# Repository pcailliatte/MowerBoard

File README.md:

# MowerBoard

---

**MowerBoard** est une unité de contrôle électronique (ECU) alternative, robuste et 100% open-source pour tracteurs tondeuses autoportées thermiques.

L'objectif principal de ce projet est de fournir une solution logicielle et matérielle entièrement libre. En mettant à disposition l'intégralité des schémas de conception, des fichiers de fabrication et du code source, nous démocratisons l'accès à une technologie généralement propriétaire et verrouillée par les fabricants.

---

---

## ⚡ À Propos de ce Projet

> **⚠️ Important :** Je suis un **maker amateur passionné par l'électronique**, pas un professionnel de l'ingénierie ni de la motoculture. 
> 
> Ce projet est développé **sur mon temps libre** et représente mon apprentissage et mes expériences personnelles. **Il peut contenir des erreurs de conception, des mauvaises pratiques ou des défauts** que je ne pourrais pas identifier seul.
>
> Je partage ce travail dans un esprit collaboratif et éducatif. Si tu utilises ce projet, sois conscient que :
> - La conception peut ne pas être optimale
> - Il n'y a pas de validation professionnelle ou de certification
> - Des améliorations et corrections peuvent être nécessaires
> - **Toute erreur reste ta responsabilité personnelle**
> - Le support n'est disponible que sur la base du temps libre disponible
>
> **Je t'encourage vivement à faire review ta réalisation par un professionnel** avant une utilisation critique.

---

## 📋 Table des matières

- [À Propos de ce Projet](#-à-propos-de-ce-projet)
- [Machine Cible](#-machine-cible)
- [État du projet](#-état-du-projet)
- [Caractéristiques principales](#-caractéristiques-principales)
- [Spécifications techniques](#-spécifications-techniques)
- [Télémétrie & Home Assistant](#-télémétrie--home-assistant)
- [Coût estimé](#-coût-estimé)
- [Installation & Démarrage](#-installation--démarrage)
- [Structure du projet](#-structure-du-projet)
- [Clause de non-responsabilité](#-clause-de-non-responsabilité--risques-critiques)
- [Licence](#-licence)
- [Contributions](#-contributions--état-du-projet)

---

## 🎯 Machine Cible

**MowerBoard** a été conçu et développé pour : **STAUB BLIZZARD 107 L 16 KH (2019)**

- **Moteur :** EMAK K1600 AVD (16 ch, 452 cm³)
- **Année :** 2019
- **Tension système :** 12V batterie

Cette ECU remplace le contrôleur d'origine de ce tracteur de pelouse, offrant une solution open-source robuste et facilement hackable.

### Portabilité & Forks

Bien que spécifiquement adapté au STAUB BLIZZARD 107 L, le design modulaire permet des adaptations pour d'autres tracteurs de pelouse avec architecture similaire.

Si tu adaptes pour un autre modèle, crée un fork et documente tes changements ! 🍴

---

## 🚦 État du projet

| Aspect | Statut |
|--------|--------|
| **Statut global** | 🛠️ Développement en cours |
| **Phase actuelle** | 🧪 Version alpha |
| **Hardware** | ✅ Saisie terminée (KiCad 10) |
| **Firmware** | 🔄 Écriture initiale en cours (C brut, microcontrôleur AVR) |
| **Structure du dépôt** | 🔄 Organisation en cours |
| **Documentation** | 🔄 En cours |
| **Release stable** | ⏳ Non disponible |

---

## 🚀 Caractéristiques principales

*   **✨ Matériel et Code 100% Libres :** Accès total aux schémas électroniques, fichiers de routage (PCB) et code source du firmware sans restriction d'accès. Inspiré par la philosophie du mouvement open-source.

*   **🛡️ Architecture Robuste :** Conçu spécifiquement pour l'environnement difficile d'un véhicule thermique (vibrations, parasites électromagnétiques induits par l'allumage, variations de tension de batterie, humidité).

*   **🔒 Logique de Sécurité Centralisée :** Gestion stricte et déterministe des boucles de sécurité critiques :
    - Détection de présence siège
    - Engagement/désengagement des lames
    - Position du point mort
    - Frein de parking
    - Arrêt d'urgence matériel
    - **Failsafe matérielle** : DO_EN en pulldown → coupage automatique des sorties en cas de watchdog

*   **⚡ Contrôle de Puissance Intégré :** Commande directe des actionneurs avec protections adaptées :
    - Embrayage électromagnétique de lame
    - Solénoïde de démarreur
    - Gestion thermique et overcurrent

*   **📊 Diagnostic & Télémétrie LoRa :** Support des interfaces de communication pour logging et diagnostic :
    - Communication série UART
    - **Télémétrie longue portée via LoRa** (Wio-E5-LE de Seeed en modem)
    - Monitoring à distance et diagnostics temps-réel (non-critique pour la sécurité)
    - **Intégration Home Assistant** pour domotique locale

*   **💰 Solution Économique :** Coût matériel estimé **~100€** pour fabriquer une carte (bien inférieur aux solutions propriétaires commerciales)

---

## 🛠 Spécifications Techniques

Le projet est divisé en deux domaines totalement ouverts :

### Architecture

*   **Cœur temps-réel :** AVR128DB (boucles de sécurité déterministes, contrôle des actionneurs)
*   **Modem LoRa :** Wio-E5-LE de Seeed (télémétrie optionnelle, non-critique)
*   **Failsafe matérielle :** DO_EN en pulldown garantit l'arrêt en cas de défaillance du MCU

### Hardware (Matériel)

*   **Outil de conception :** KiCad 10
*   **Fichiers fournis :**
    - Schémas de principe détaillés
    - Routage de puissance et signaux
    - Nomenclature complète (BOM)
    - Fichiers Gerber (prêts pour fabrication PCB)
*   **Microcontrôleur principal :** AVR128DB
*   **Module LoRa :** Wio-E5-LE de Seeed (STM32WLE5xx)
*   **Tensions supportées :** 12V batterie, régulation embarquée

### Firmware (Code)

*   **Langage :** C brut (pas de couche d'abstraction matérielle)
*   **Compilateur :** MPLAB X / XC Compiler
*   **Caractéristiques :**
    - Boucles de sécurité déterministes temps-réel
    - Gestion des modes de veille (économie d'énergie)
    - Communication séries (UART)
    - Watchdog matériel et software
    - Failsafe électronique : perte de contrôle → arrêt automatique

### Module LoRa (Télémétrie)

*   **Module :** Seeed Wio-E5-LE (fonctionne en modem indépendant)
*   **Protocole :** LoRaWAN / LoRa
*   **Fonction :** Transmission longue portée des données de diagnostic et de télémétrie
*   **Avantages :** 
    - Portée jusqu'à plusieurs kilomètres
    - Faible consommation énergétique
    - Non-critique pour la sécurité (arrêt indépendant du LoRa)

---

## 📱 Télémétrie & Home Assistant

Le module LoRa transmet les données de la tondeuse vers une gateway LoRaWAN locale, intégrée dans **Home Assistant**.

### Données remontées

**Phase 1 (MVP) :**
- **Horamètre** : Cumul des heures de fonctionnement
- **Tension batterie** : État de charge et diagnostic

**Phase 2 (futur) :**
- Température moteur
- Cycle des lames
- Diagnostics avancés

### Architecture

```
ECU (Wio-E5-LE) 
    ↓ LoRa
Gateway LoRaWAN Seeed
    ↓ Ethernet/WiFi
Home Assistant (local)
    ↓
Dashboard / Alertes / Automations
```

### Utilité

- **Monitoring à distance** : Suivi de l'état depuis le canapé
- **Historique** : Logs des heures de tonte
- **Alertes** : Notification si batterie faible, etc.
- **Automations** : Intégration avec d'autres services domotiques

> **Note :** La télémétrie est **optionnelle et non-critique**. La tondeuse fonctionne normalement même si le LoRa est déconnecté.

---

## 💰 Coût estimé

**Coût de fabrication prévu : ~100€** (pour une carte complète, pièce unique)

Cette estimation inclut :
- PCB (fabrication industrielle)
- Composants électroniques (résistances, condensateurs, ICs)
- Module LoRa Wio-E5-LE
- Connecteurs et éléments passifs
- Régulateur 12V et protections

**Cette solution est significativement moins coûteuse que les ECU propriétaires du marché**, tout en offrant des capacités équivalentes ou supérieures.

> **Note :** Le coût peut varier selon les fournisseurs, les quantités commandées et les taux de change. Cette estimation est basée sur les prix courants des composants (2024). En production de volume, le coût pourrait être réduit.

---

## 🚀 Installation & Démarrage

### Prérequis

**Pour le Hardware :**
- KiCad 10.0+
- Outils de fabrication PCB (si fabrique soi-même)
- Composants électroniques (voir BOM)

**Pour le Firmware :**
- MPLAB X IDE
- Compiler XC8 (Microchip)
- Programmateur AVR (ex : PICKIT5)

**Pour la Télémétrie (optionnel) :**
- Home Assistant (installation locale)
- Gateway LoRaWAN Seeed (WM1302, etc.)

### Étapes de mise en place

#### 1. Cloner le dépôt
```bash
git clone https://github.com/pcailliatte/MowerBoard.git
cd MowerBoard
```

#### 2. Hardware - Fabriquer la carte
- Ouvrir les fichiers KiCad dans `Hardware/`
- Exporter les fichiers Gerber
- Envoyer à un fabricant PCB (ex : JLCPCB, PCBway)
- Souder les composants (voir BOM pour la liste complète)

#### 3. Firmware - Compiler et flasher
```bash
cd Firmware/
mplab build
# Programmer via AVR ISP
```

#### 4. Télémétrie (optionnel)
- Configurer la gateway LoRaWAN dans Home Assistant
- Flasher le firmware LoRa sur le Wio-E5-LE
- Ajouter les sensors dans Home Assistant

---

## 📁 Structure du projet

⚠️ **La structure du dépôt est actuellement en cours d'organisation. Les chemins et répertoires ci-dessous reflètent la vision finale du projet.**

```
MowerBoard/
├── Hardware/
│   ├── STAUB_BLIZZARD_107L/
│   │   ├── Schematics/      # Schémas électroniques KiCad
│   │   ├── PCB/             # Fichiers de routage et Gerber
│   │   ├── BOM.csv          # Nomenclature des composants
│   │   └── Doc/             # Documentation hardware spécifique
│   └── Generic/             # Composants réutilisables pour autres modèles
├── Firmware/
│   ├── src/                 # Code source C
│   ├── include/             # En-têtes
│   ├── Makefile             # Build configuration
│   └── Doc/                 # Documentation firmware
├── LoRa/
│   ├── src/                 # Code LoRa / Wio-E5-LE
│   ├── telemetry/           # Schéma de télémétrie
│   └── Doc/                 # Documentation LoRa & Home Assistant
├── Doc/
│   ├── assets/              # Images et ressources
│   ├── DESIGN.md            # Rationale de conception
│   ├── ASSEMBLY.md          # Guide d'assemblage
│   ├── SAFETY.md            # Guides de sécurité
│   └── COMPATIBILITY.md     # Compatibilité avec autres modèles
├── README.md                # Ce fichier
├── CONTRIBUTING.md          # Guide de contribution
└── LICENCE.md               # Licence du hardware (CERN-OHL-S v2)

```

---

## ⚠️ Clause de Non-Responsabilité & Risques Critiques

### 🚨 DANGER DE MORT ET DE BLESSURES GRAVES

Un tracteur tondeuse est une machine lourde dotée d'un plateau de coupe rotatif à haute vitesse. **Vos actions de conception, de soudure, de câblage, de programmation et d'intégration de cette carte vous engagent personnellement.**

#### Responsabilité absolue de vos actions

*   L'intégration de cette carte, la modification du faisceau électrique d'origine, le flashage du firmware et le **shunt volontaire ou involontaire** des boucles de sécurité construites **relèvent de votre seule responsabilité légale et pénale.**
*   Une défaillance de cette ECU peut entraîner :
    - La perte de contrôle du moteur
    - L'engagement involontaire des lames de coupe
    - La perte du freinage d'urgence
    - **Des blessures graves ou mortelles**

#### Absence de Garantie

Ce projet est fourni **"en l'état"**, à des fins éducatives et de recherche, **sans aucune garantie d'aucune sorte**, expresse ou implicite, quant à sa sécurité, sa fiabilité, sa conformité légale ou son fonctionnement.

#### Limitation de Responsabilité

En aucun cas les auteurs, contributeurs ou titulaires du copyright ne pourront être tenus responsables des dommages directs, indirects, accessoires ou consécutifs (incluant mais non limités aux blessures, décès, dommages matériels) résultant de l'utilisation ou de l'abus de ce projet.

#### Statut du Projet & Expertise

**Je suis un maker amateur passionné par l'électronique**, développant ce projet **sur mon temps libre**, pas un professionnel de l'ingénierie ni de l'industrie agro-mécanique. **Ce projet peut contenir des erreurs de conception, des défauts, ou des mauvaises pratiques** que je n'aurais pas identifiés seul.

**Je te recommande vivement de faire valider ta réalisation par un professionnel qualifié** avant toute utilisation sur une machine réelle.

#### Conformité légale & Assurance

Avant toute intégration :
- ✅ Consultez un ingénieur agréé
- ✅ Vérifiez la conformité réglementaire locale
- ✅ Contactez votre assurance
- ✅ Faites review votre travail par un professionnel
- ✅ Testez exhaustivement dans un environnement isolé et sécurisé

---

## 📜 Licence

Ce dépôt réunit deux domaines publiés sous deux licences distinctes :

| Dossier | Licence | Texte complet |
|---------|---------|---------------|
| `Hardware/` | **CERN Open Hardware Licence - Strongly Reciprocal v2 (CERN-OHL-S v2)** | [`LICENCE.md`](LICENCE.md) |
| `Firmware/` (hors `config.mcc/`) | **GNU GPL v3 ou ultérieure**, avec une permission additionnelle pour le code généré par MCC (`GPL-3.0-or-later WITH GPL-3.0-linking-source-exception`) | [`Firmware/LICENSE`](Firmware/LICENSE) |
| `Firmware/config.mcc/` | Licence Microchip (code généré par MPLAB Code Configurator) | En-tête de chaque fichier |

### Hardware : CERN-OHL-S v2

*   **Partage et Fork :** Vous êtes libre de copier, modifier et distribuer les sources matérielles (schémas, PCB, BOM).

*   **Attribution :** Vous devez conserver la mention du copyright d'origine et l'attribution au projet MowerBoard dans tous les travaux dérivés.

*   **Usage Commercial :** La fabrication et la vente commerciale de cette carte **sont autorisées**, à condition de respecter les clauses ci-dessous.

*   **Copyleft Fort (Pas de prise de contrôle) :** Si vous modifiez le matériel ou les schémas et que vous les distribuez, ou que vous distribuez des cartes fabriquées à partir de ces sources, **vous avez l'obligation de publier l'intégralité des sources modifiées** sous la même licence CERN-OHL-S v2.

### Firmware : GPL-3.0-or-later avec exception MCC

*   **Partage et Fork :** Vous êtes libre d'utiliser, d'étudier, de modifier et de redistribuer le firmware.

*   **Copyleft :** Si vous distribuez le firmware, modifié ou non, y compris sous forme binaire ou flashé sur une carte, **vous devez fournir le code source correspondant** sous GPL-3.0-or-later.

*   **Anti-verrouillage :** Lorsque le firmware est distribué dans un produit grand public (« User Product » au sens de la section 6 de la GPL v3), le distributeur doit fournir, en plus des sources, les informations nécessaires pour installer et exécuter une version modifiée du firmware sur la carte (« Installation Information »). Un bootloader verrouillé ou une signature qui empêcherait de flasher un firmware modifié n'est donc pas permis. Cette obligation ne s'applique pas si personne, pas même le distributeur, ne peut mettre à jour le firmware de l'appareil.

*   **Exception MCC :** Une permission additionnelle (section 7 de la GPL v3) autorise la liaison avec le code généré par Microchip MCC, qui reste sous licence Microchip. Le code source correspondant d'un binaire doit alors inclure aussi le code MCC utilisé.

### Marque

*   **Aucun droit de marque :** Vous ne pouvez pas utiliser le nom "MowerBoard" pour des produits dérivés sans permission explicite.

---

## 👥 Contributions

Ce dépôt centralise l'ingénierie partagée du projet. Les schémas, nomenclatures (BOM) et codes sources sont documentés ouvertement au fur et à mesure du développement.

### Comment contribuer ?

1. **Fork le projet** sur GitHub
2. **Créer une branche** (`git checkout -b feature/ma-contribution`)
3. **Soumettre une Pull Request** avec une description claire
4. **Attendre la review** des contributeurs

### Directives de contribution

*   Respectez la structure existante du projet
*   Testez votre code avant de le soumettre
*   Documentez vos changements
*   Utilisez des messages de commit clairs en français ou anglais
*   Respectez la licence du domaine concerné : CERN-OHL-S v2 pour `Hardware/`, GPL-3.0-or-later pour `Firmware/`

### Signalement de bugs

Utilisez l'onglet Issues pour signaler des bugs ou suggérer des améliorations.

**Consultez le fichier `CONTRIBUTING.md` pour des directives détaillées.**

---

## 📚 Documentation supplémentaire

- [Guide de contribution](CONTRIBUTING.md)
- [Guide d'assemblage](Doc/ASSEMBLY.md)
- [Design & Architecture](Doc/DESIGN.md)
- [Guide de sécurité](Doc/SAFETY.md)
- [Compatibilité & Portabilité](Doc/COMPATIBILITY.md)
- [FAQ & Troubleshooting](Doc/FAQ.md)

---

## 🔗 Ressources externes

*   [KiCad Documentation](https://docs.kicad.org/)
*   [CERN Open Hardware Licence](https://ohwr.org/cern_ohl_v2_how_to_use.pdf)
*   [Microchip AVR Documentation](https://www.microchip.com/)
*   [Seeed Wio-E5-LE Documentation](https://wiki.seeedstudio.com/Wio_E5_series_LoRa_Module/)
*   [Home Assistant Documentation](https://www.home-assistant.io/)
*   [Seeed LoRaWAN Gateway](https://wiki.seeedstudio.com/Gateway_LoRaWAN/)

---

## ✉️ Contact & Support

*   **Issues GitHub :** Pour les bugs et questions techniques
*   **Discussions GitHub :** Pour les échanges communautaires

---

**Dernière mise à jour :** Juillet 2026
**Maintaineur :** [@pcailliatte](https://github.com/pcailliatte) (maker amateur passionné développant sur temps libre)

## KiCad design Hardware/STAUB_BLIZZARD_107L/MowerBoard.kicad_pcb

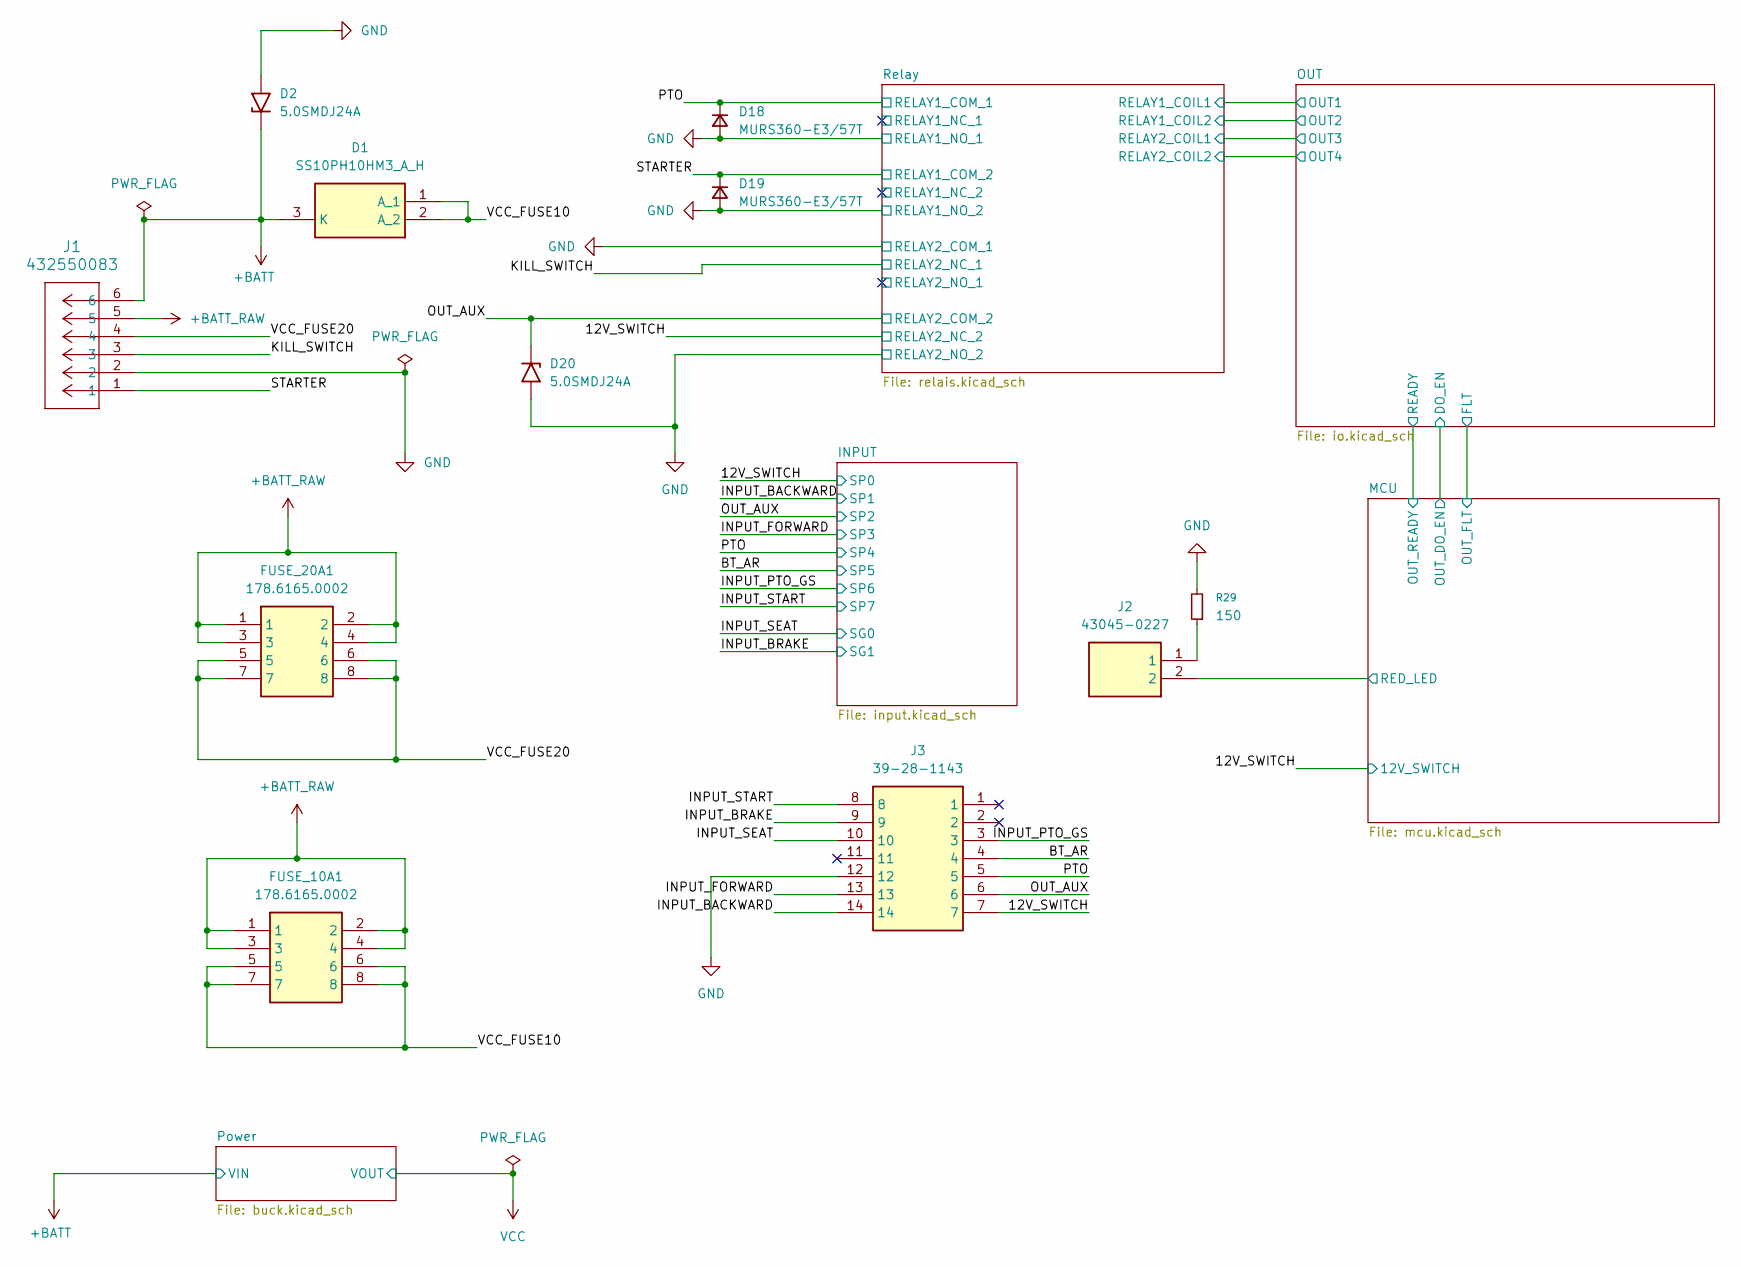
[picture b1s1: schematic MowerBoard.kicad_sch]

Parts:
D1: SS10PH10HM3_A_H; V10PN50M387A; Mouser Part Number 78-SS10PH10HM3_A/H
D2, D20: 5.0SMDJ24A; D_SMC; Mouser Part Number 576-5.0SMDJ24A
D18, D19: MURS360-E3/57T; D_SMC
FUSE_10A1, FUSE_20A1: 178.6165.0002; 17861650002; Mouser Part Number 576-178.6165.0002
J1: 432550083; CONN_SDA_43255-00xx_06_MOL
J2: 43045-0227; 43045-02YY_272829; Mouser Part Number 538-43045-0227
J3: 39-28-1143; Mouser Part Number 538-39-28-1143
R29: 150; R_0603_1608Metric

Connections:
+BATT: D1.3 (K), D2.1 (A1), J1.6; also elsewhere on the board
+BATT_RAW: FUSE_10A1.1, FUSE_10A1.2, FUSE_10A1.3, FUSE_10A1.4, FUSE_20A1.1, FUSE_20A1.2, FUSE_20A1.3, FUSE_20A1.4, J1.5
/12V_SWITCH: J3.7; also elsewhere on the board
/BT_AR: J3.4; also elsewhere on the board
/INPUT_BACKWARD: J3.14; also elsewhere on the board
/INPUT_BRAKE: J3.9; also elsewhere on the board
/INPUT_FORWARD: J3.13; also elsewhere on the board
/INPUT_PTO_GS: J3.3; also elsewhere on the board
/INPUT_SEAT: J3.10; also elsewhere on the board
/INPUT_START: J3.8; also elsewhere on the board
/KILL_SWITCH: J1.3; also elsewhere on the board
/MCU/RED_LED: J2.2; also elsewhere on the board
/OUT_AUX: D20.1 (A1), J3.6; also elsewhere on the board
/PTO: D18.1 (K), J3.5; also elsewhere on the board
/STARTER: D19.1 (K), J1.1; also elsewhere on the board
/VCC_FUSE10: D1.1 (A_1), D1.2 (A_2), FUSE_10A1.5, FUSE_10A1.6, FUSE_10A1.7, FUSE_10A1.8
/VCC_FUSE20: FUSE_20A1.5, FUSE_20A1.6, FUSE_20A1.7, FUSE_20A1.8, J1.4
GND: D2.2 (A2), D18.2 (A), D19.2 (A), D20.2 (A2), J1.2, J3.12, R29.2; also elsewhere on the board
unnamed: J2.1, R29.1

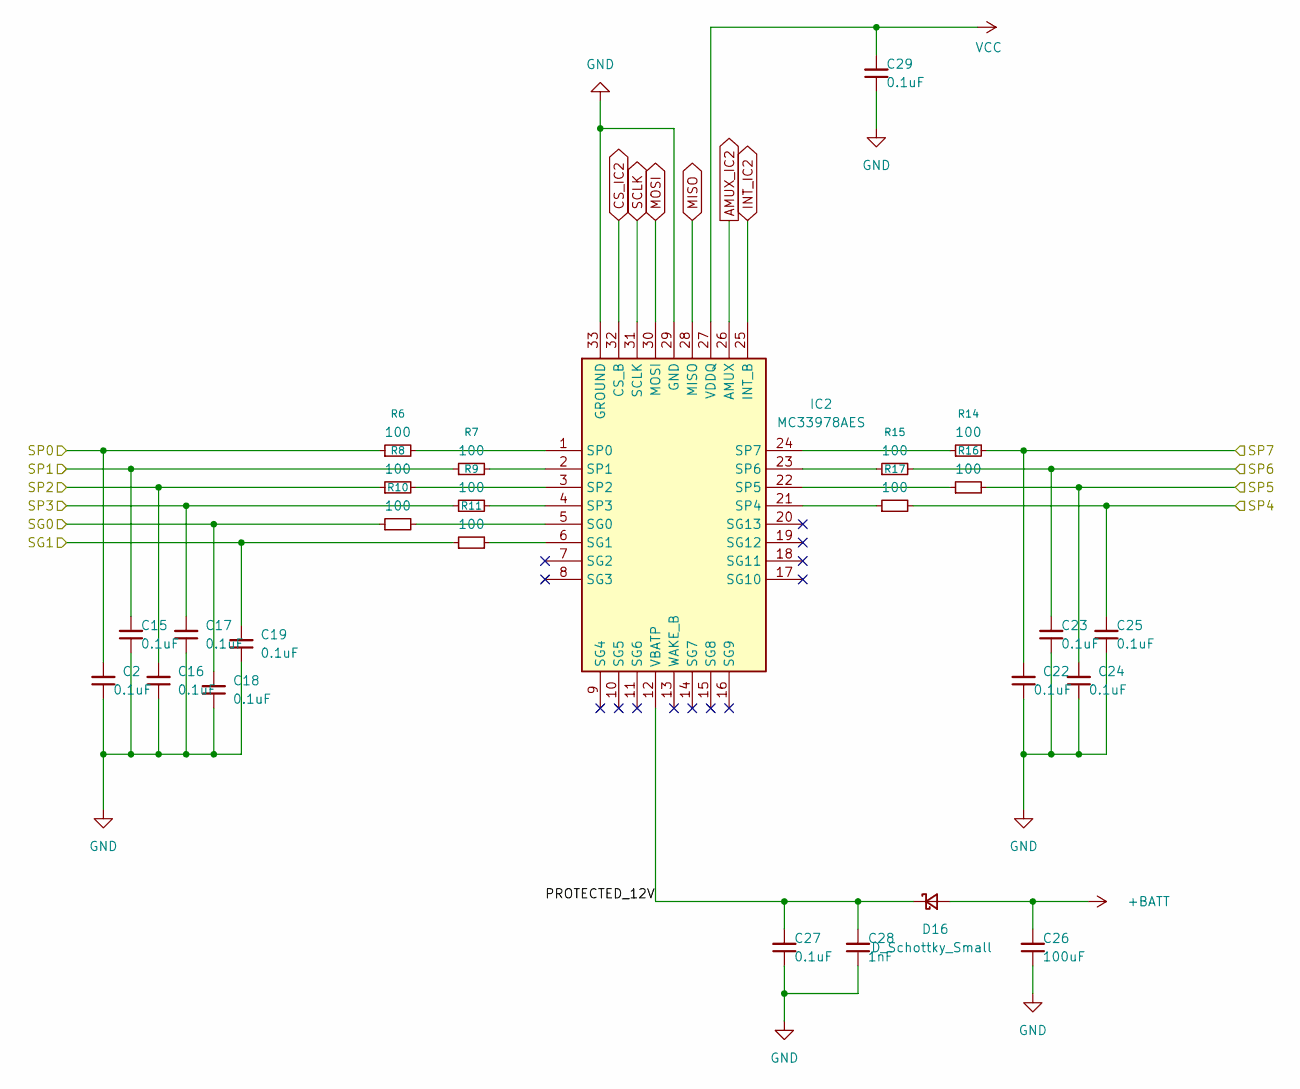
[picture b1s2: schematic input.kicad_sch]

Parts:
C2, C15, C16, C17, C18, C19, C22, C23, C24, C25, C27, C29: 0.1uF; C_0402_1005Metric
C26: 100uF; CP_Elec_6.3x5.7
C28: 1nF; C_0402_1005Metric
D16: D_Schottky_Small; Nexperia_CFP3_SOD-123W
IC2: MC33978AES; QFN50P500X500X90-33N-D; Mouser Part Number 841-MC33978AES
R6, R7, R8, R9, R10, R11, R14, R15, R16, R17: 100; R_0603_1608Metric

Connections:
+BATT: C26.2, D16.2 (A); also elsewhere on the board
/12V_SWITCH: C2.2, R6.1; also elsewhere on the board
/BT_AR: C24.2, R16.2; also elsewhere on the board
/INPUT/PROTECTED_12V: C27.2, C28.2, D16.1 (K), IC2.12 (VBATP)
/INPUT_BACKWARD: C15.2, R7.1; also elsewhere on the board
/INPUT_BRAKE: C19.2, R11.1; also elsewhere on the board
/INPUT_FORWARD: C17.2, R9.1; also elsewhere on the board
/INPUT_PTO_GS: C23.2, R15.2; also elsewhere on the board
/INPUT_SEAT: C18.2, R10.1; also elsewhere on the board
/INPUT_START: C22.2, R14.2; also elsewhere on the board
/OUT_AUX: C16.2, R8.1; also elsewhere on the board
/PTO: C25.2, R17.2; also elsewhere on the board
AMUX_IC2: IC2.26 (AMUX); also elsewhere on the board
CS_IC2: IC2.32 (CS_B); also elsewhere on the board
GND: C2.1, C15.1, C16.1, C17.1, C18.1, C19.1, C22.1, C23.1, C24.1, C25.1, C26.1, C27.1, C28.1, C29.1, IC2.29 (GND), IC2.33 (GROUND); also elsewhere on the board
INT_IC2: IC2.25 (INT_B); also elsewhere on the board
MISO: IC2.28 (MISO); also elsewhere on the board
MOSI: IC2.30 (MOSI); also elsewhere on the board
unnamed: IC2.5 (SG0), R10.2
unnamed: IC2.6 (SG1), R11.2
unnamed: IC2.1 (SP0), R6.2
unnamed: IC2.2 (SP1), R7.2
unnamed: IC2.3 (SP2), R8.2
unnamed: IC2.4 (SP3), R9.2
unnamed: IC2.21 (SP4), R17.1
unnamed: IC2.22 (SP5), R16.1
unnamed: IC2.23 (SP6), R15.1
unnamed: IC2.24 (SP7), R14.1
SCLK: IC2.31 (SCLK); also elsewhere on the board
VCC: C29.2, IC2.27 (VDDQ); also elsewhere on the board

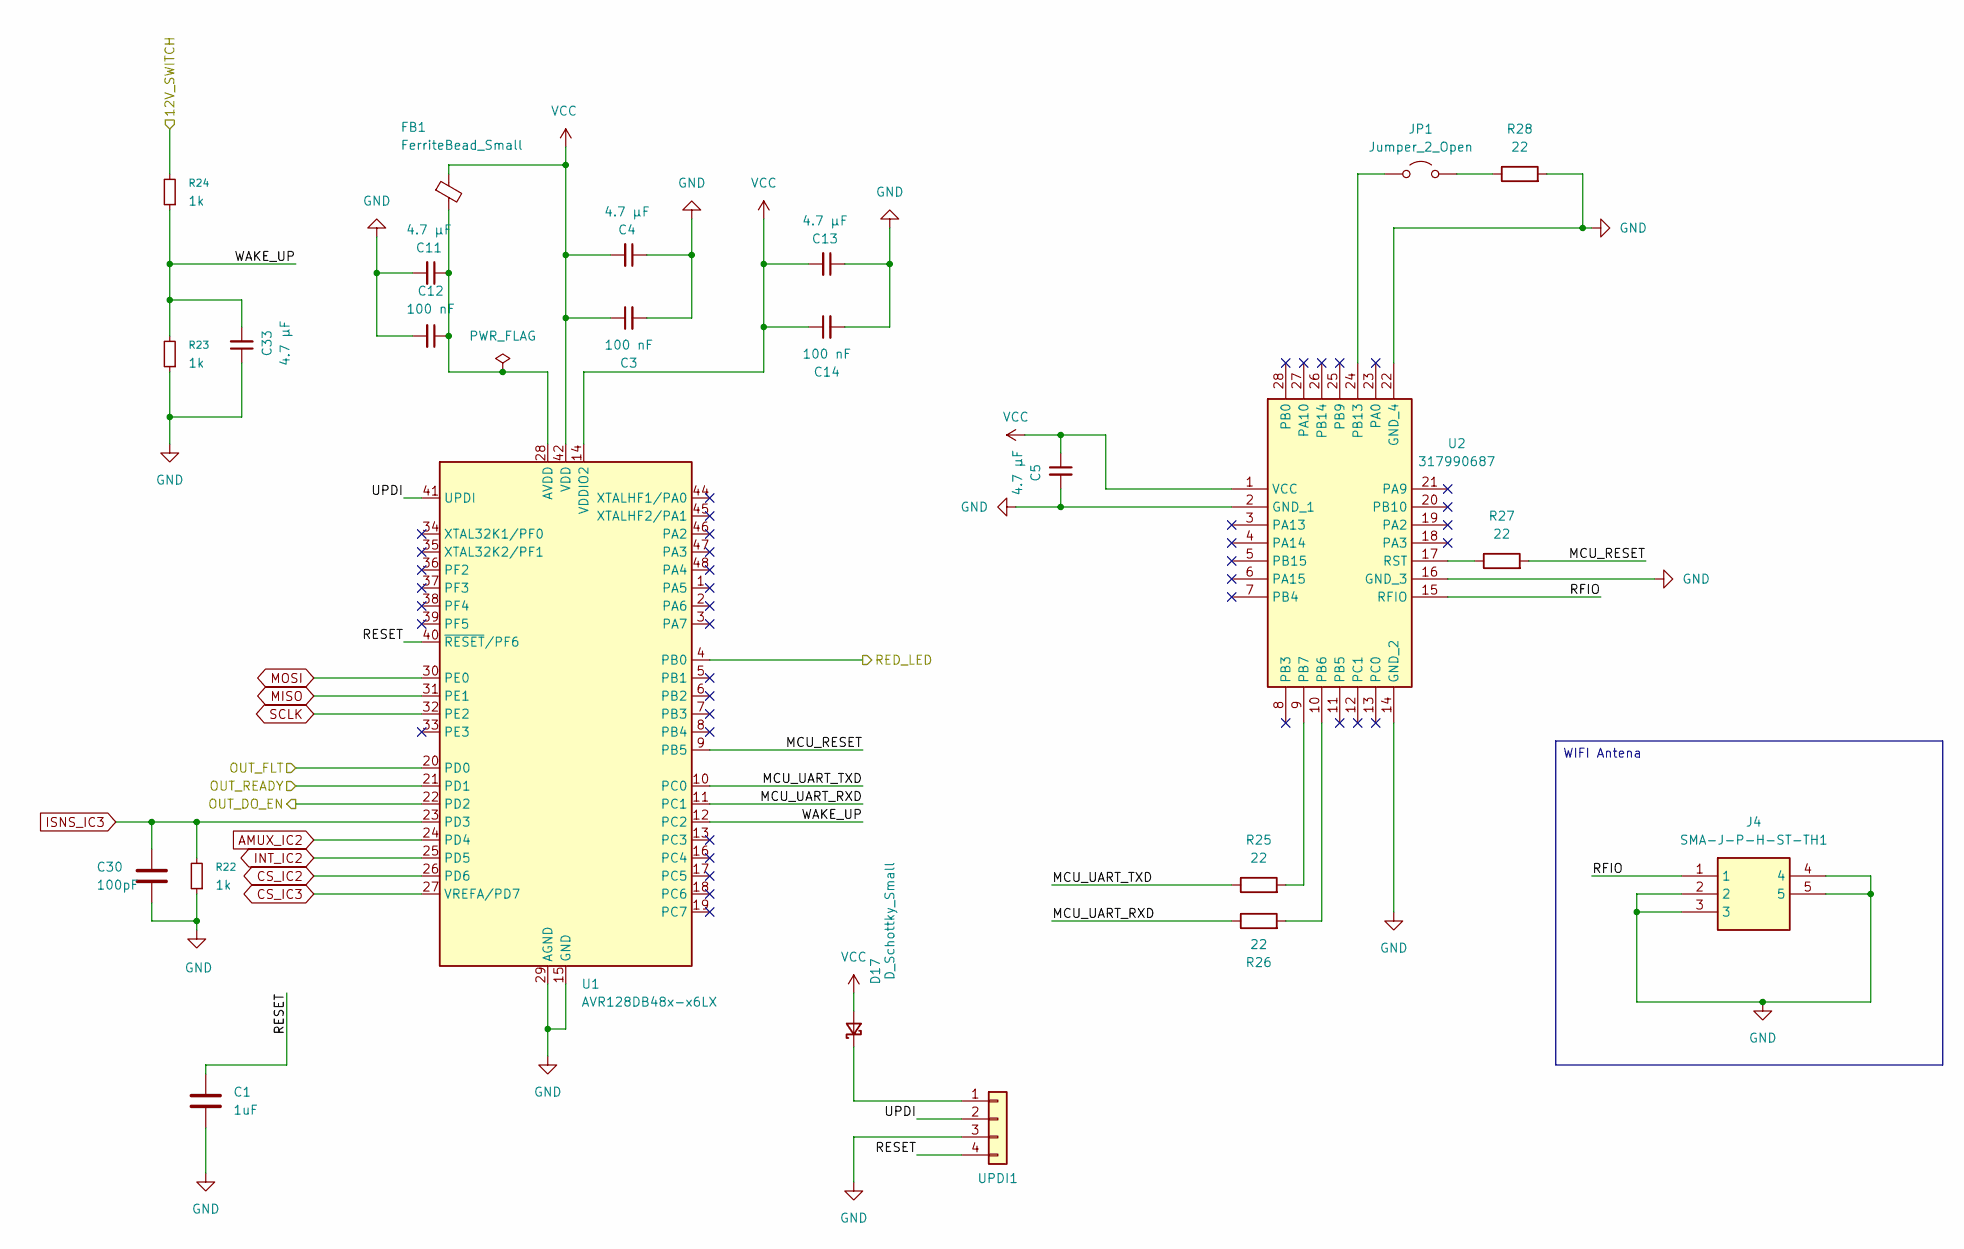
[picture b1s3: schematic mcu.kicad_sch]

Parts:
C1: 1uF; C_0402_1005Metric
C3, C12, C14: 100 nF; C_0402_1005Metric
C4, C5, C11, C13, C33: 4.7 µF; C_0402_1005Metric
C30: 100pF; C_0402_1005Metric
D17: D_Schottky_Small; Nexperia_CFP3_SOD-123W
FB1: FerriteBead_Small; R_0603_1608Metric_Pad0.98x0.95mm_HandSolder
J4: SMA-J-P-H-ST-TH1; SMAJPHSTTH1; Mouser Part Number 200-SMAJPHSTTH1
JP1: Jumper_2_Open; PinHeader_1x02_P2.54mm_Vertical
R22, R23, R24: 1k; R_0603_1608Metric
R25, R26, R27, R28: 22; R_0603_1608Metric
U1: AVR128DB48x-x6LX; QFN-48-1EP_6x6mm_P0.4mm_EP4.2x4.2mm
U2: 317990687; Mouser Part Number 713-317990687
UPDI1: PinHeader_1x04_P2.54mm_Vertical

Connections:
/12V_SWITCH: R24.2; also elsewhere on the board
/MCU/MCU_RESET: R27.2, U1.9 (PB5)
/MCU/MCU_UART_RXD: R26.1, U1.11 (PC1)
/MCU/MCU_UART_TXD: R25.1, U1.10 (PC0)
/MCU/OUT_FLT: U1.20 (PD0); also elsewhere on the board
/MCU/OUT_READY: U1.21 (PD1); also elsewhere on the board
/MCU/RED_LED: U1.4 (PB0); also elsewhere on the board
/MCU/RESET: C1.1, U1.40 (~RESET/PF6), UPDI1.4
/MCU/RFIO: J4.1, U2.15 (RFIO)
/MCU/UPDI: U1.41 (UPDI), UPDI1.2
/MCU/WAKE_UP: C33.2, R23.2, R24.1, U1.12 (PC2)
/OUT/DO_EN: U1.22 (PD2); also elsewhere on the board
AMUX_IC2: U1.24 (PD4); also elsewhere on the board
CS_IC2: U1.26 (PD6); also elsewhere on the board
CS_IC3: U1.27 (VREFA/PD7); also elsewhere on the board
GND: C1.2, C3.2, C4.1, C5.2, C11.2, C12.2, C13.1, C14.2, C30.2, C33.1, J4.2, J4.3, J4.4, J4.5, R22.1, R23.1, R28.2, U1.15 (GND), U1.29 (AGND), U1.43 (GND), U1.49 (GND), U2.2 (GND_1), U2.14 (GND_2), U2.16 (GND_3), U2.22 (GND_4), UPDI1.3; also elsewhere on the board
INT_IC2: U1.25 (PD5); also elsewhere on the board
ISNS_IC3: C30.1, R22.2, U1.23 (PD3); also elsewhere on the board
MISO: U1.31 (PE1); also elsewhere on the board
MOSI: U1.30 (PE0); also elsewhere on the board
unnamed: D17.1 (K), UPDI1.1
unnamed: JP1.1 (A), U2.24 (PB13)
unnamed: JP1.2 (B), R28.1
unnamed: C11.1, C12.1, FB1.2, U1.28 (AVDD)
unnamed: R26.2, U2.10 (PB6)
unnamed: R25.2, U2.9 (PB7)
unnamed: R27.1, U2.17 (RST)
SCLK: U1.32 (PE2); also elsewhere on the board
VCC: C3.1, C4.2, C5.1, C13.2, C14.1, D17.2 (A), FB1.1, U1.14 (VDDIO2), U1.42 (VDD), U2.1 (VCC); also elsewhere on the board

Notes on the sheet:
WIFI Antena

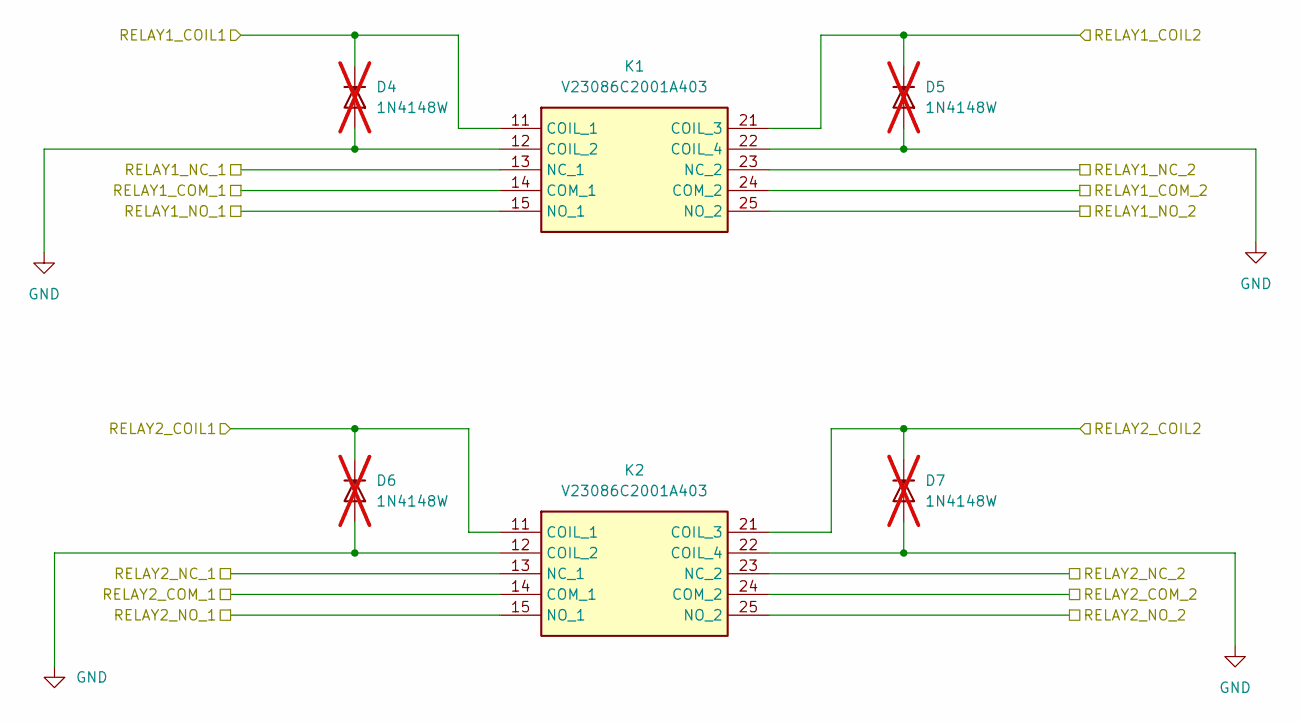
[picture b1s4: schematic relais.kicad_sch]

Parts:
D4, D5, D6, D7: 1N4148W; D_SOD-123; not fitted
K1, K2: V23086C2001A403; Mouser Part Number 571-1413009-9

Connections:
/12V_SWITCH: K2.23 (NC_2); also elsewhere on the board
/KILL_SWITCH: K2.13 (NC_1); also elsewhere on the board
/OUT/OUT1: D4.1 (K), K1.11 (COIL_1); also elsewhere on the board
/OUT/OUT2: D5.1 (K), K1.21 (COIL_3); also elsewhere on the board
/OUT/OUT3: D6.1 (K), K2.11 (COIL_1); also elsewhere on the board
/OUT/OUT4: D7.1 (K), K2.21 (COIL_3); also elsewhere on the board
/OUT_AUX: K2.24 (COM_2); also elsewhere on the board
/PTO: K1.14 (COM_1); also elsewhere on the board
/Relay/RELAY1_NC_1: K1.13 (NC_1)
/Relay/RELAY1_NC_2: K1.23 (NC_2)
/Relay/RELAY2_NO_1: K2.15 (NO_1)
/STARTER: K1.24 (COM_2); also elsewhere on the board
GND: D4.2 (A), D5.2 (A), D6.2 (A), D7.2 (A), K1.12 (COIL_2), K1.15 (NO_1), K1.22 (COIL_4), K1.25 (NO_2), K2.12 (COIL_2), K2.14 (COM_1), K2.22 (COIL_4), K2.25 (NO_2); also elsewhere on the board

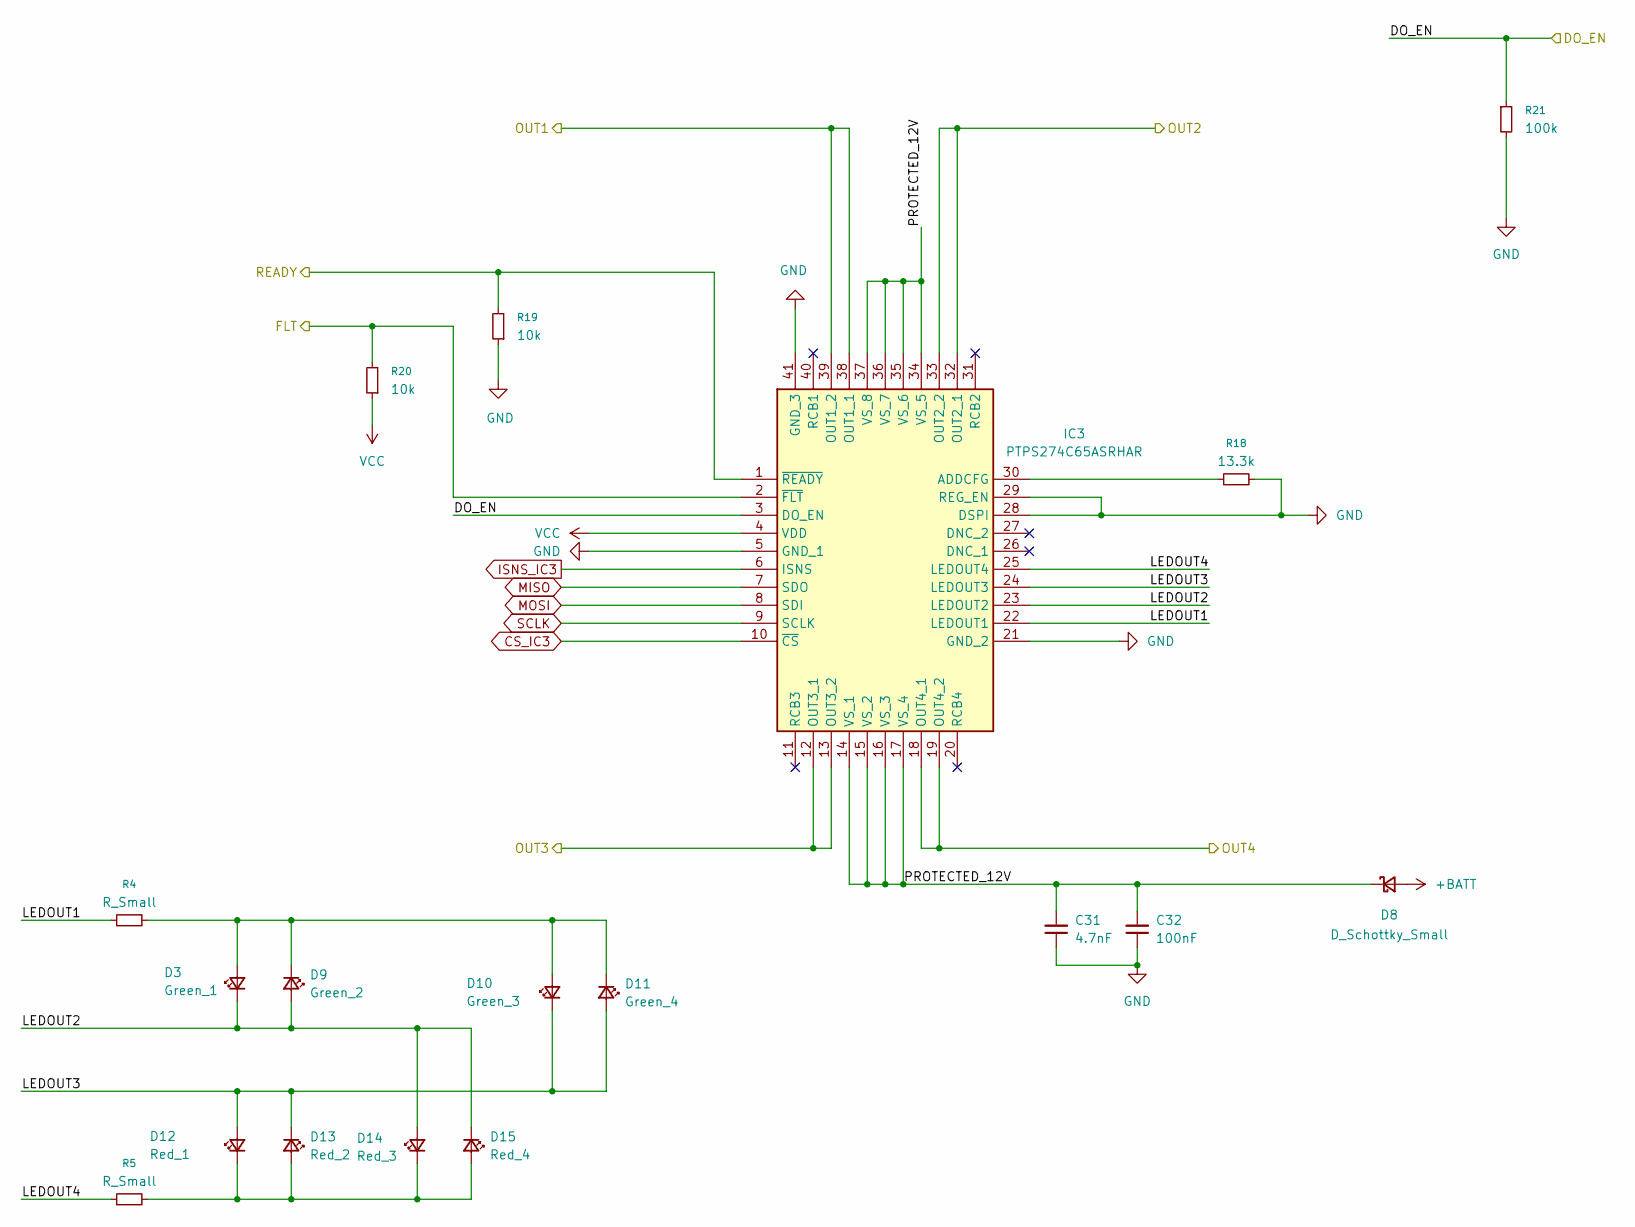
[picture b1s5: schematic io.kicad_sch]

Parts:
C31: 4.7nF; C_0402_1005Metric
C32: 100nF; C_0402_1005Metric
D3: Green_1; LED_0603_1608Metric
D8: D_Schottky_Small; Nexperia_CFP3_SOD-123W
D9: Green_2; LED_0603_1608Metric
D10: Green_3; LED_0603_1608Metric
D11: Green_4; LED_0603_1608Metric
D12: Red_1; LED_0603_1608Metric
D13: Red_2; LED_0603_1608Metric
D14: Red_3; LED_0603_1608Metric
D15: Red_4; LED_0603_1608Metric
IC3: PTPS274C65ASRHAR; QFN50P600X600X100-41N-D; Manufacturer_Part_Number PTPS274C65ASRHAR
R4, R5: R_Small; R_0603_1608Metric
R18: 13.3k; R_0603_1608Metric
R19, R20: 10k; R_0603_1608Metric
R21: 100k; R_0603_1608Metric

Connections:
+BATT: D8.2 (A); also elsewhere on the board
/MCU/OUT_FLT: IC3.2 (~FLT), R20.2; also elsewhere on the board
/MCU/OUT_READY: IC3.1 (~READY), R19.2; also elsewhere on the board
/OUT/DO_EN: IC3.3 (DO_EN), R21.1; also elsewhere on the board
/OUT/LEDOUT1: IC3.22 (LEDOUT1), R4.1
/OUT/LEDOUT2: D3.1 (K), D9.2 (A), D14.2 (A), D15.1 (K), IC3.23 (LEDOUT2)
/OUT/LEDOUT3: D10.1 (K), D11.2 (A), D12.2 (A), D13.1 (K), IC3.24 (LEDOUT3)
/OUT/LEDOUT4: IC3.25 (LEDOUT4), R5.1
/OUT/OUT1: IC3.38 (OUT1_1), IC3.39 (OUT1_2); also elsewhere on the board
/OUT/OUT2: IC3.32 (OUT2_1), IC3.33 (OUT2_2); also elsewhere on the board
/OUT/OUT3: IC3.12 (OUT3_1), IC3.13 (OUT3_2); also elsewhere on the board
/OUT/OUT4: IC3.18 (OUT4_1), IC3.19 (OUT4_2); also elsewhere on the board
/OUT/PROTECTED_12V: C31.2, C32.2, D8.1 (K), IC3.14 (VS_1), IC3.15 (VS_2), IC3.16 (VS_3), IC3.17 (VS_4), IC3.34 (VS_5), IC3.35 (VS_6), IC3.36 (VS_7), IC3.37 (VS_8)
CS_IC3: IC3.10 (~CS); also elsewhere on the board
GND: C31.1, C32.1, IC3.5 (GND_1), IC3.21 (GND_2), IC3.28 (DSPI), IC3.29 (REG_EN), IC3.41 (GND_3), R18.2, R19.1, R21.2; also elsewhere on the board
ISNS_IC3: IC3.6 (ISNS); also elsewhere on the board
MISO: IC3.7 (SDO); also elsewhere on the board
MOSI: IC3.8 (SDI); also elsewhere on the board
unnamed: D3.2 (A), D9.1 (K), D10.2 (A), D11.1 (K), R4.2
unnamed: D12.1 (K), D13.2 (A), D14.1 (K), D15.2 (A), R5.2
unnamed: IC3.30 (ADDCFG), R18.1
SCLK: IC3.9 (SCLK); also elsewhere on the board
VCC: IC3.4 (VDD), R20.1; also elsewhere on the board

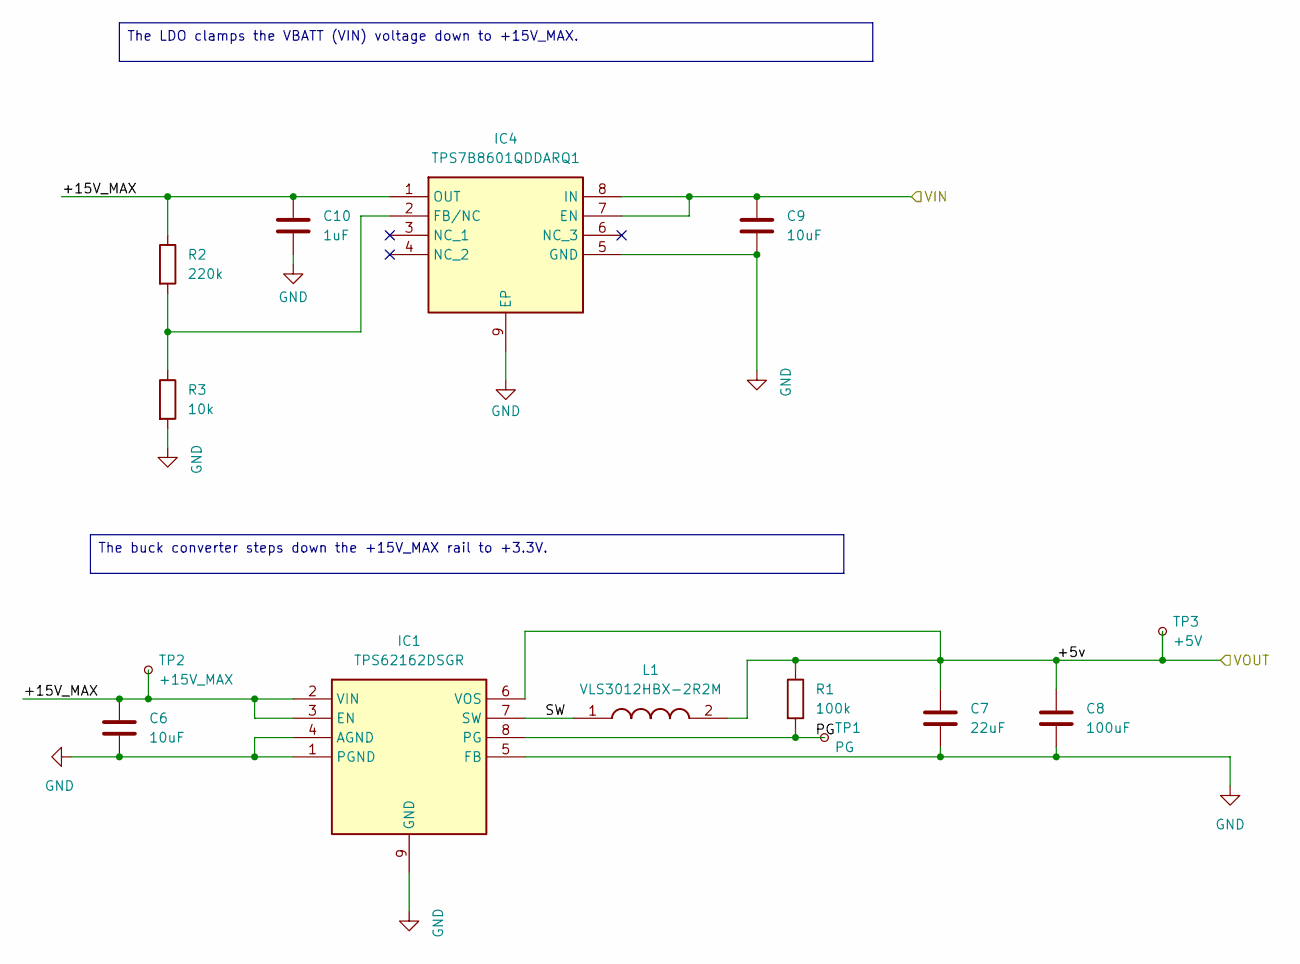
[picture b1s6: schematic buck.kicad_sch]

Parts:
C6, C9: 10uF; C_0805_2012Metric
C7: 22uF; C_0805_2012Metric
C8: 100uF; CP_Elec_6.3x5.7
C10: 1uF; C_0805_2012Metric
IC1: TPS62162DSGR; SON50P200X200X80-9N; Mouser Part Number 595-TPS62162DSGR
IC4: TPS7B8601QDDARQ1; SOIC127P600X170-9N; Mouser Part Number 595-TPS7B8601QDDARQ1
L1: VLS3012HBX-2R2M; VLS3012; Mouser Part Number 810-VLS3012HBX-2R2M
R1: 100k; R_0603_1608Metric
R2: 220k; R_0603_1608Metric
R3: 10k; R_0603_1608Metric
TP1: PG; TestPoint_Pad_1.0x1.0mm
TP2: +15V_MAX; TestPoint_Pad_1.0x1.0mm
TP3: +5V; TestPoint_Pad_1.0x1.0mm

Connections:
+BATT: C9.1, IC4.7 (EN), IC4.8 (IN); also elsewhere on the board
/Power/+15V_MAX: C6.1, C10.1, IC1.2 (VIN), IC1.3 (EN), IC4.1 (OUT), R2.1, TP2.1 (1_1)
/Power/PG: IC1.8 (PG), R1.2, TP1.1 (1_1)
/Power/SW: IC1.7 (SW), L1.1
GND: C6.2, C7.2, C8.2, C9.2, C10.2, IC1.1 (PGND), IC1.4 (AGND), IC1.5 (FB), IC1.9 (GND), IC4.5 (GND), IC4.9 (EP), R3.2; also elsewhere on the board
unnamed: IC4.2 (FB/NC), R2.2, R3.1
VCC: C7.1, C8.1, IC1.6 (VOS), L1.2, R1.1, TP3.1 (1_1); also elsewhere on the board

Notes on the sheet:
The buck converter steps down the +15V_MAX rail to +3.3V.
The LDO clamps the VBATT (VIN) voltage down to +15V_MAX.

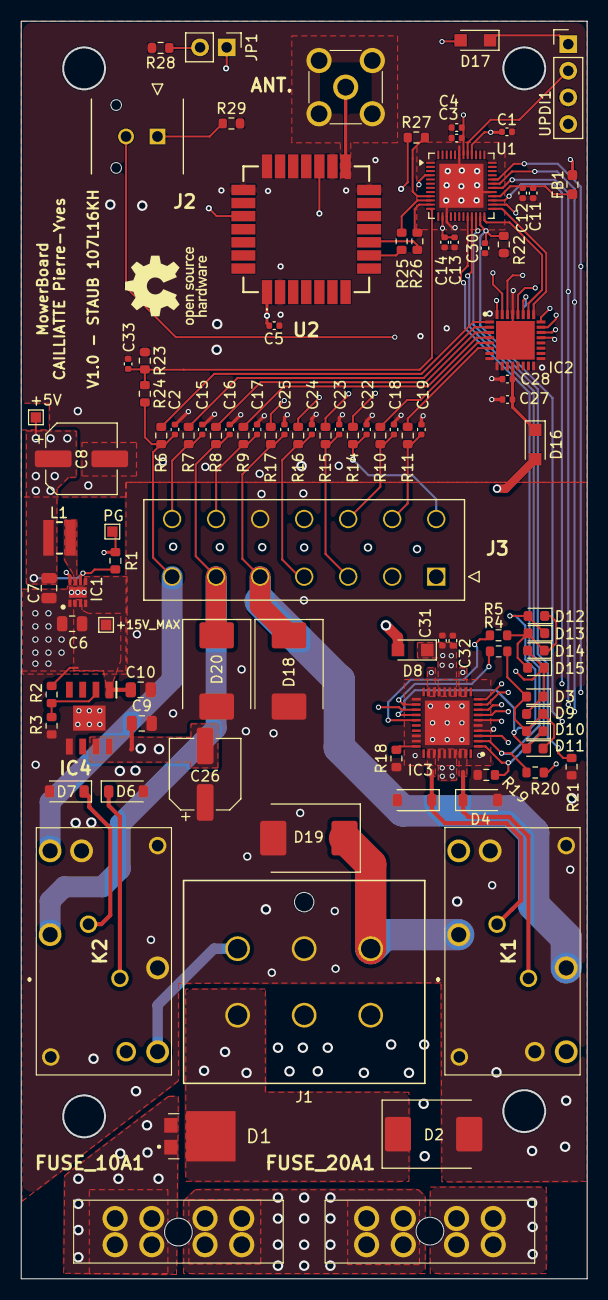
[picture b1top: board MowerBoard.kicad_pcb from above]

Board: 4 copper layers, 54.0 x 120.0 mm, 99 parts (1 on the bottom side), 72 nets.
